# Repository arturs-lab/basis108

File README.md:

# basis108
Document my computer Basis 108 and its components. Organize various bits of documentation from 3rd parties that I've found across the web.

It is not my intent to violate any rights of Copyright/Trade Mark owners here. If any lawful rights owner finds content here which they do not wish included here, please contact me and I will promptly remove such content.

# History
I bought my Basis 108 in Netherlands around 1990. It appears to be a kit or early version of this computer as compared to production version that I've found traces of out on the internet. My copy came enclosed in home made case made of stainless steel with main board mounted on wooden straps glued to it. Floppy drives were mounted using metal straps resembling those found in kid's construction kits. main boards itself has no silkscreen but appears to have been produced and assembled in factory. A separate keyboard was included which was controlled by its own processor and sent keystrokes to the computer over a parallel flat ribbon cable. Sadly, this keyboard was lost.

# Platform
This computer appears to be a clone of Apple ][ with Z80 processor integrated into the main board. This allowed it to not only run Apple DOS but also CP/M. I have disks with CP/M 2.2 and 3.0. I spent most of my time in the latter writing programs in Turbo Pascal 3.0 and Z80 assembly. Besides the main board and floppy drives, the machine came with a built in power supply delivering +12, +5, -5 and -12V. I no longer have this power supply and use PC power supply instead. It also came with a Floppy Drive Controller. This controller appears to have two connectors for a typical Apple format Floppy drives. It also has some additional circuitry and what appears to be a Shugart style interface which is connected to two Teac FD-55F-03-U drives. These drives appear to have been modified to allow 80 or 40 track operation controlled by a switch mounted on front panel of computer.

# Please help!
If anyone out there has more information about this computer, please reach out to me and share what you have so that I may 8nclude it in this archive.

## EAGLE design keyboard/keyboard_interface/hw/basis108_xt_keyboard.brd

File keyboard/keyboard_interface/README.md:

Since original keyboard that came with my Basis108 was lost, I had to create an interface to connect another keyboard to it. 
At the time XT style keyboards were still popular and in use and were much easier to interface than the new PS2 style keyboards.
This is the original version of the keyboard interface that I built. It has some problems with autorepeat and fast keystrokes. This is perhaps due to serial interface being bit-banged since the microcontroller that I used did not have a serial port.

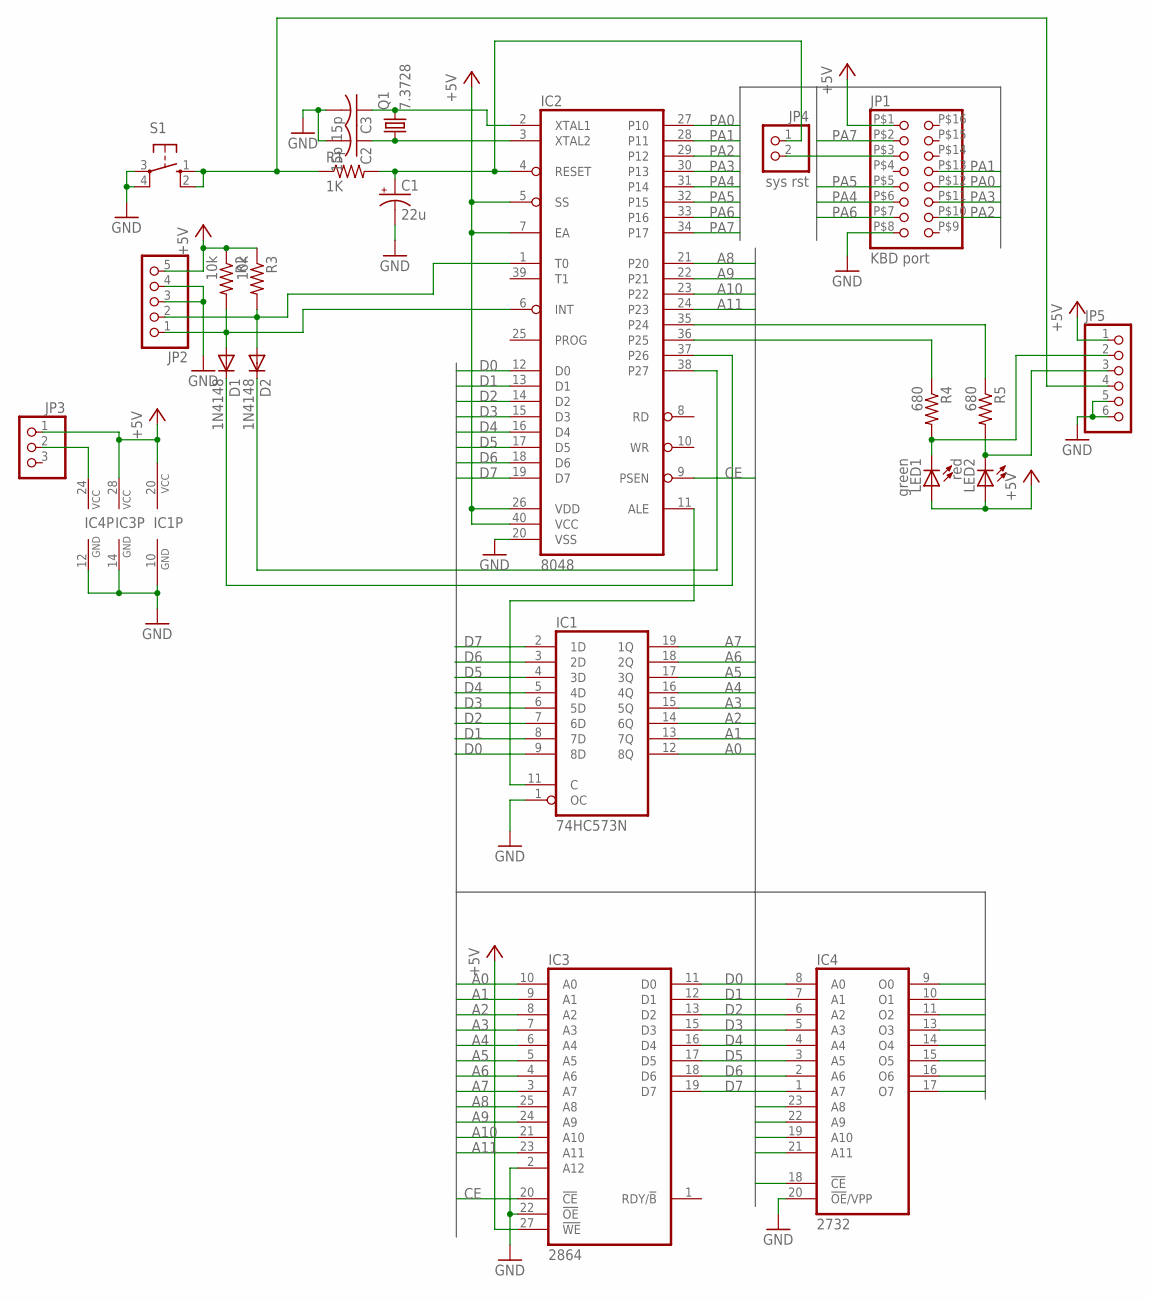
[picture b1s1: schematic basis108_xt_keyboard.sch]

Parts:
C1: 22u; E2,5-6
C2, C3: 15p; C025-040X050
D1, D2: 1N4148; DO35-7
IC1: 74HC573N; DIL20
IC2: 8048; DIL40
IC3: 2864; DIL28
IC4: 2732; DIL24
JP1: KBD port; 2X8DIL
JP2: PINHD-1X5; 1X05
JP3: PINHD-1X3; 1X03
JP4: sys rst; 1X02
JP5: PINHD-1X6; 1X06
LED1: green; LED3MM
LED2: red; LED3MM
Q1: 7.3728; HC49U-H
R1: 1K; 0204/7
R2, R3: 10k; 0204/7
R4, R5: 680; 0204/7
S1: 10-XX; B3F-10XX

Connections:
+5V: IC1.20 (VCC), IC2.5 (SS), IC2.7 (EA), IC2.26 (VDD), IC2.40 (VCC), IC3.27 (!WE), IC3.28 (VCC), JP1.P$1 (1), JP2.5, JP3.1, JP5.1, LED1.A, LED2.A, R2.1, R3.1
A0: IC1.12 (8Q), IC3.10 (A0), IC4.8 (A0)
A1: IC1.13 (7Q), IC3.9 (A1), IC4.7 (A1)
A2: IC1.14 (6Q), IC3.8 (A2), IC4.6 (A2)
A3: IC1.15 (5Q), IC3.7 (A3), IC4.5 (A3)
A4: IC1.16 (4Q), IC3.6 (A4), IC4.4 (A4)
A5: IC1.17 (3Q), IC3.5 (A5), IC4.3 (A5)
A6: IC1.18 (2Q), IC3.4 (A6), IC4.2 (A6)
A7: IC1.19 (1Q), IC3.3 (A7), IC4.1 (A7)
A8: IC2.21 (P20), IC3.25 (A8), IC4.23 (A8)
A9: IC2.22 (P21), IC3.24 (A9), IC4.22 (A9)
A10: IC2.23 (P22), IC3.21 (A10), IC4.19 (A10)
A11: IC2.24 (P23), IC3.23 (A11), IC4.21 (A11)
ALE: IC1.11 (C), IC2.11 (ALE)
CE: IC2.9 (PSEN), IC3.20 (!CE), IC4.18 (!CE)
D0: IC1.9 (8D), IC2.12 (D0), IC3.11 (D0), IC4.9 (O0)
D1: IC1.8 (7D), IC2.13 (D1), IC3.12 (D1), IC4.10 (O1)
D2: IC1.7 (6D), IC2.14 (D2), IC3.13 (D2), IC4.11 (O2)
D3: IC1.6 (5D), IC2.15 (D3), IC3.15 (D3), IC4.13 (O3)
D4: IC1.5 (4D), IC2.16 (D4), IC3.16 (D4), IC4.14 (O4)
D5: IC1.4 (3D), IC2.17 (D5), IC3.17 (D5), IC4.15 (O5)
D6: IC1.3 (2D), IC2.18 (D6), IC3.18 (D6), IC4.16 (O6)
D7: IC1.2 (1D), IC2.19 (D7), IC3.19 (D7), IC4.17 (O7)
GND: C1.-, C2.2, C3.2, IC1.1 (OC), IC1.10 (GND), IC2.20 (VSS), IC3.2 (A12), IC3.14 (GND), IC3.22 (!OE), IC4.12 (GND), IC4.20 (!OE!/VPP), JP1.P$8 (15), JP2.3, JP2.4, JP5.5, JP5.6, S1.3, S1.4 (P1)
unnamed: C2.1, IC2.3 (XTAL2), Q1.1
unnamed: C3.1, IC2.2 (XTAL1), Q1.2
unnamed: C1.+, IC2.4 (RESET), JP4.1, R1.2
unnamed: IC4.24 (VCC), JP3.2
unnamed: JP5.4, R1.1, S1.1 (S), S1.2 (S1)
unnamed: D1.A, IC2.6 (INT), JP2.1, R2.2
unnamed: D2.A, IC2.1 (T0), JP2.2, R3.2
unnamed: D2.C, IC2.38 (P27)
unnamed: D1.C, IC2.37 (P26)
unnamed: IC2.36 (P25), R4.1
unnamed: IC2.35 (P24), R5.1
unnamed: JP5.3, LED2.K (C), R5.2
unnamed: JP5.2, LED1.K (C), R4.2
unnamed: JP1.P$3 (5), JP4.2
PA0: IC2.27 (P10), JP1.P$12 (10)
PA1: IC2.28 (P11), JP1.P$13 (8)
PA2: IC2.29 (P12), JP1.P$10 (14)
PA3: IC2.30 (P13), JP1.P$11 (12)
PA4: IC2.31 (P14), JP1.P$6 (11)
PA5: IC2.32 (P15), JP1.P$5 (9)
PA6: IC2.33 (P16), JP1.P$7 (13)
PA7: IC2.34 (P17), JP1.P$2 (3)

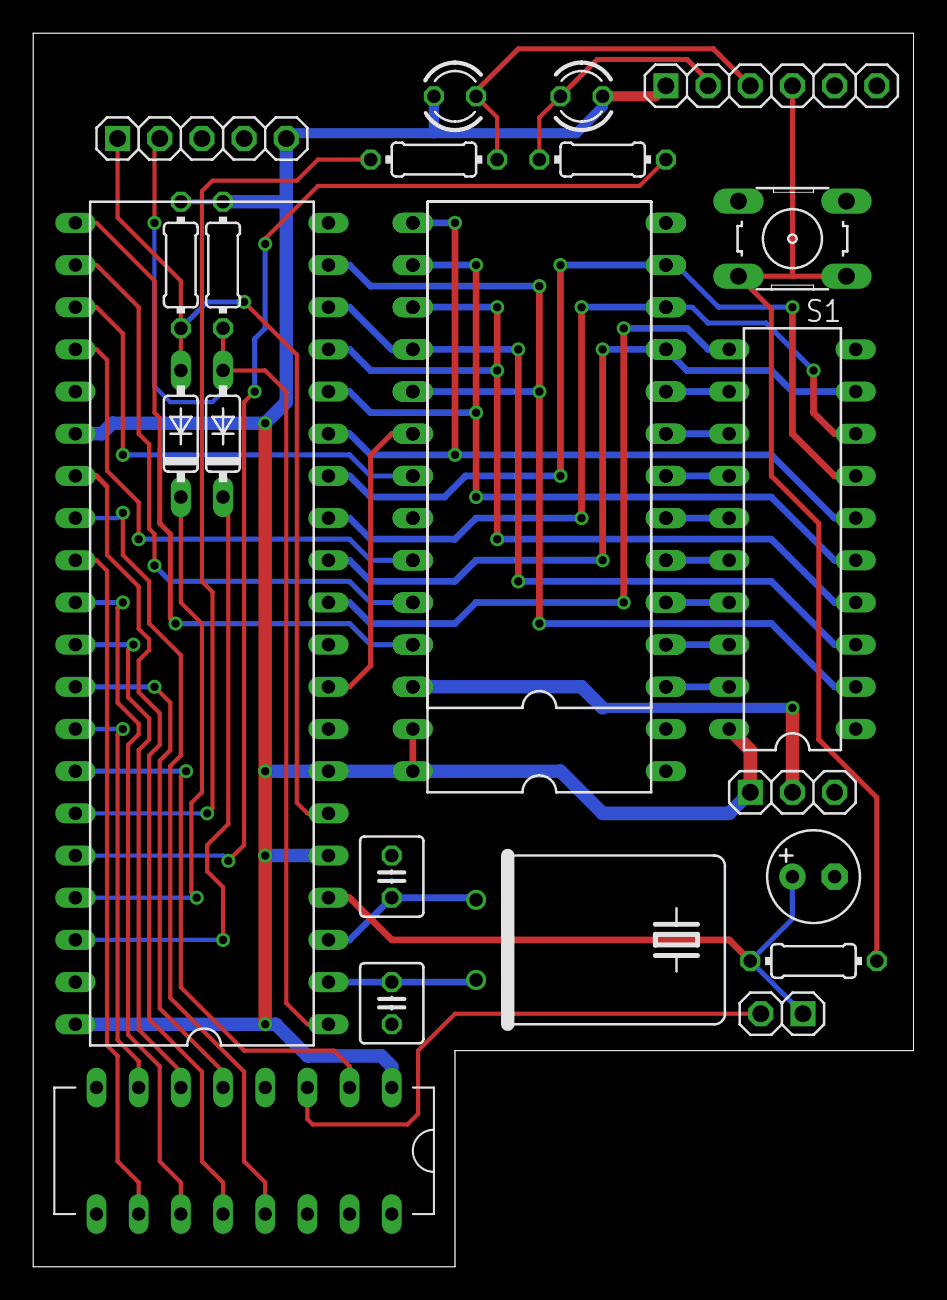
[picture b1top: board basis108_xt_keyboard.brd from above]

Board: 2 copper layers, 53.0 x 74.3 mm, 23 parts (0 on the bottom side), 46 nets.

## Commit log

2025-05-03 Update README.md
    Initial version of README
2025-05-04 clean up images to minimize storage
2025-05-05 More EPROM images and descriptions.
2025-05-05 more details about EPROMs
2025-05-05 Floppy controller add TBP28L22 ROM dump
2025-05-11 Add information about floppy drive connection. Data signal timings
2025-05-11 Add info about floppy controller
2025-05-11 Add readme file for commercial version with some info about basis108.zip file
2025-05-11 Add documentation for Apple II computer
2025-05-18 Add more images for cloppy drive
2025-05-18 add images for floppy controller
2025-05-18 add images of main board
2025-05-18 reverse engineering CP/M boot process
2025-05-18 commercial version manual - another version with searchable text
2025-05-18 main board schematic
2025-05-18 ps2 keyboard interface
2025-05-18 more details on reverse engineering
2025-05-18 Update cpm_boot_sectors.txt
    Add results of call to $b00
2025-05-18 Update cpm_boot_sectors.txt
    Notes on call to $3c6
2025-05-18 Update cpm_boot_sectors.txt
    Placing jump to monitor at $3cf results in OS booting normally instead
2025-05-18 Update README.md
    Correct wording
2025-05-19 update reverse_eng/README.md and cpm boot sector
2025-05-19 update reverse_eng/d5_rom.txt and cpm boot sector
2025-05-19 update reverse_eng cpm boot sector
2025-05-20 record work on restoring seemingly corrupt EPROM
2025-05-29 add missing entries to chip map
